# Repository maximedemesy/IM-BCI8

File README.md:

# IM-BCI8

**A low-cost 8-channel wireless EEG / Brain-Computer Interface platform based on the ADS1299 and ESP32-S3.**

> **Project status:** Active development / experimental prototype  
> **Intended use:** Education, research, experimentation and BCI development  
> **Not a medical device**

IM-BCI8 is a personal open-hardware EEG project designed to explore how accessible a complete Brain-Computer Interface platform can be made using readily available components, open-source hardware, 3D printing and modern development tools.

The system combines an **8-channel ADS1299 analog front-end**, an **ESP32-S3**, battery operation, Wi-Fi connectivity, a browser-based acquisition interface and a dry-electrode headset based on the **OpenBCI Ultracortex Mark IV**.

The goal of this repository is to make the complete prototype reproducible and understandable: electronics, firmware, assembly information, mechanical files, characterization data and troubleshooting procedures are progressively being documented here.

---

## Why this project?

IM-BCI8 originally started as a personal side project and as a gift, but quickly evolved into a broader engineering experiment.

Commercial EEG platforms can make experimenting with Brain-Computer Interfaces expensive, particularly for students, makers and independent developers.

The **OpenBCI ecosystem and Cyton board were major inspirations for this project**. Their work demonstrated how open hardware can make biosignal acquisition considerably more accessible.

IM-BCI8 does not aim to replace OpenBCI.

Instead, it explores a more integrated and low-cost architecture focused on:

- low prototype cost;
- simple wireless operation;
- no external acquisition dongle;
- a browser-based user interface hosted directly by the device;
- compatibility with an existing open-source 3D-printable headset;
- dry-electrode experimentation;
- easy modification of both hardware and firmware.

The current prototype costs approximately **$150 USD for the PCB and electronic components** in one-off quantities.

The complete headset adds approximately **$70 USD**, including dry electrodes, wiring, springs, mechanical hardware and 3D-printing material.

This puts the current complete experimental setup at roughly **$220 USD in material cost**.

These figures are approximate prototype costs and exclude assembly labor, tools, shipping, import duties and development time.

---

## System architecture

The current platform is built around a relatively simple architecture:

```text
Dry EEG electrodes
        │
        ▼
   Input filtering
        │
        ▼
     ADS1299
  8-channel AFE
        │
       SPI
        │
        ▼
    ESP32-S3
        │
        ├── Wi-Fi
        ├── Web interface
        ├── Recording
        └── OTA updates

LiPo battery
    │
    ├── 3.3 V digital rail
    ├── 3.3 V analog rail
    └── ~5 V analog rail

USB-C
    │
    ├── Firmware / development
    └── LiPo charging
```

---

## Current hardware

The current IM-BCI8 prototype includes:

- 8 EEG acquisition channels
- Texas Instruments ADS1299 24-bit biopotential analog front-end
- ESP32-S3 microcontroller
- 250 samples per second acquisition
- Wi-Fi communication
- Integrated web interface hosted directly by the ESP32
- Wireless firmware updates
- Single-cell LiPo battery operation
- Integrated battery charger
- Common reference electrode
- BIAS electrode
- Dry EEG electrodes
- Compatibility with a 3D-printable Ultracortex-based headset

The current electrode layout used during development is:

`Fp1 — Fp2 — C3 — C4 — P7 — P8 — O1 — O2`

with separate reference and BIAS electrodes.

---

## Browser-based interface

One of the main design goals of IM-BCI8 is reducing the amount of software required to start experimenting.

The ESP32-S3 hosts its own Wi-Fi network and web interface.

A computer or smartphone can therefore connect directly to the board and access the acquisition interface from a standard web browser.

The current interface provides:

- eight-channel live EEG visualization;
- separated channel plots and individual channel identification;
- configurable signal scaling;
- FFT / frequency-spectrum visualization;
- Delta, Theta, Alpha and Beta band visualization;
- electrode mapping;
- internal ADS1299 test modes;
- experimental event markers;
- CSV recording;
- firmware configuration;
- OTA firmware updates.

No dedicated acquisition dongle is required.

---

## Headset and mechanical design

The headset itself was **not designed as part of IM-BCI8**.

The current prototype uses the official 3D-printable files from the **OpenBCI Ultracortex Mark IV**, together with community-developed electrode-holder designs.

These existing open-source mechanical designs made it possible to focus the project primarily on the electronics, firmware, integration and experimentation rather than redesigning an EEG headset from scratch.

Most of the mechanical components used in the current build therefore originate from the OpenBCI ecosystem or community contributions.

One part had to be recreated specifically for this prototype: a **comfort electrode-holder tip / insert**, because the exact part required for the selected electrode mount could not be found as an available printable file.

The IM-BCI8 electronics enclosure and its integration with the headset are also documented separately where applicable.

All third-party mechanical files included or referenced by this repository will retain appropriate attribution and licensing information.

The current headset uses approximately **$70 USD of material and components**, including:

- dry electrodes;
- wiring;
- springs;
- screws and mechanical hardware;
- reference / BIAS contacts;
- 3D-printing material.

Detailed sourcing and assembly information will be provided in the `mechanical/` and `docs/` directories.

---

## AI-assisted development

Artificial intelligence played a significant role in the development of this project.

This is a personal side project, and one of my priorities was to iterate quickly and explore ideas without spending unnecessary time on repetitive development tasks.

Tools including **OpenAI GPT-5.6** and **Google Gemini** were used throughout different stages of the project, including:

- brainstorming and architecture discussions;
- hardware-design review;
- datasheet interpretation and design checks;
- firmware development;
- web-interface development;
- debugging;
- documentation;
- repository organization;
- test-procedure development.

A significant portion of the ESP32 firmware and browser interface was developed using an AI-assisted, or effectively **“vibe-coded,”** workflow.

AI assistance was also used when discussing and refining parts of the electronic architecture and when preparing documentation for this repository.

This does **not** mean that generated output was assumed to be correct.

Hardware decisions were checked against datasheets and measurements, firmware was tested on the actual device, and the behavior of the complete system was progressively validated experimentally.

AI is treated here as a development and prototyping tool rather than as a substitute for engineering verification.

I am documenting this explicitly because transparency about how the project was created is part of the open-source philosophy of IM-BCI8.

---

## Current development status

IM-BCI8 is **not a finished commercial product**.

The first hardware prototype is operational and the complete acquisition chain has been successfully tested, but characterization is still ongoing.

Current and planned validation work includes:

- electrical characterization;
- input-referred noise measurements;
- frequency-response measurements;
- channel-to-channel crosstalk;
- long-term stability;
- dry-electrode performance;
- BIAS performance;
- real EEG acquisition;
- repeatability across additional boards;
- firmware and web-interface improvements.

Raw characterization data and test procedures will progressively be added to this repository.

---

## Known design limitations

This first hardware revision was deliberately designed around simplicity, compactness and low cost.

It therefore has several known limitations that are important to understand before reproducing it.

### Battery polarity

The current revision does **not** include reverse-polarity protection on the battery input.

Connecting the battery with reversed polarity may permanently damage components.

Battery connector polarity must therefore be verified before power is applied.

### Input and component protection

The design intentionally keeps the analog front-end relatively minimal.

The EEG inputs and several sensitive components are not protected to the level expected from commercial or certified biomedical instrumentation.

Incorrect wiring, electrostatic discharge, inappropriate external equipment or accidental overvoltage may damage the board.

### Galvanic isolation

The current design does **not** provide medical-grade galvanic isolation between the USB interface and the EEG electronics.

For this reason, USB must not be connected while the system is attached to a person.

### Battery monitoring

Battery voltage is not currently measured by the ESP32.

A future revision may include a dedicated battery-voltage sensing circuit.

### Prototype robustness

This board was designed as an experimental prototype rather than as a consumer product.

Some design choices prioritize:

- minimal component count;
- compactness;
- cost;
- ease of fabrication;
- rapid iteration;

over protection against every possible misuse.

These limitations are not hidden issues: they are documented here both for safety and as potential improvement targets for future hardware revisions.

---

## ⚠️ Safety

**IM-BCI8 is experimental hardware and is not a medical device.**

When electrodes are connected to a person, the system must operate from its internal battery only.

Do not connect the board simultaneously to:

- USB;
- a charger;
- a laboratory power supply;
- a grounded oscilloscope;
- a function generator;
- other grounded laboratory equipment.

Human EEG acquisition should use:

**battery power + wireless communication only.**

Anyone reproducing or modifying this project is responsible for understanding the electrical and biological safety implications of their modifications.

A more complete safety document is available in [`SAFETY.md`](SAFETY.md).

---

## Repository structure

```text
IM-BCI8/
├── README.md
├── SAFETY.md
├── .gitignore
│
├── hardware/
│   ├── README.md
│   ├── kicad/
│   │   ├── IM-BCI8_RevA.kicad_pro
│   │   ├── IM-BCI8_RevA.kicad_sch
│   │   └── IM-BCI8_RevA.kicad_pcb
│   │
│   └── manufacturing/
│       ├── README.md
│       ├── BOM/
│       │   └── IM-BCI8_RevA_BOM.csv
│       └── gerbers/
│           └── IM-BCI8_RevA_Gerbers.zip
│
├── firmware/
│   ├── README.md
│   └── IM_BCI8_V1_3_1/
│       ├── IM_BCI8_V1_3_1.ino
│       └── secrets.example.h
│
├── mechanical/
│   ├── README.md
│   │
│   ├── derived/
│   │   └── IM-BCI8_Comfort_Tip.STL
│   │
│   ├── enclosure/
│   │   ├── IM-BCI8_Enclosure_Body.STL
│   │   └── IM-BCI8_Enclosure_Cover.STL
│   │
│   ├── earclip/
│   │   └── IM-BCI8_Compliant_Earclip.STL
│   │
│   └── upstream/
│       └── openbci-ultracortex-mark-iv/
│           ├── LICENSE.md
│           ├── UPSTREAM.md
│           │
│           ├── frame/
│           │   ├── M4_Medium_Front.stl
│           │   └── M4_Medium_Back.stl
│           │
│           ├── inserts/
│           │   └── M4_Hardware_insert_105dot5_percent.STL
│           │
│           ├── clips/
│           │   └── M4_Wire_Clip.stl
│           │
│           └── electrode-holders/
│               ├── M4_Hardware_09_Eholder.STL
│               └── M4_Hardware_09_Octabolt.STL
│
└── docs/
    └── images/
        ├── architecture.png
        ├── characterization-noise.png
        ├── headset-overview.jpg
        ├── im-bci8-hero.jpg
        └── web-interface.png
```

### `hardware/`

KiCad source files, schematics, PCB layout, BOM and manufacturing files.

### `firmware/`

ESP32-S3 firmware and the embedded browser interface.

### `mechanical/`

Mechanical files required to reproduce the current headset configuration, together with attribution to the original OpenBCI and community designs.

### `docs/`

Assembly instructions, flashing procedures, electrode wiring, first-start procedures and troubleshooting.

### `characterization/`

Measurement procedures, raw data and results used to characterize the electronics and complete system.

### `examples/`

Example EEG recordings and simple experiments performed using the platform.

---

## Open development

IM-BCI8 is intended to remain an open project.

Hardware improvements, firmware features, mechanical improvements, analysis tools, experiments and characterization data are welcome.

If you reproduce the board, test a modification, identify a design problem or develop an improvement, please consider opening an Issue or submitting a Pull Request.

Examples of useful contributions include:

- hardware protection improvements;
- analog front-end improvements;
- firmware optimization;
- additional signal-processing tools;
- BrainFlow / LSL / MNE integration;
- improved browser visualization;
- alternative electrode systems;
- additional characterization;
- replicated measurements on independently built boards;
- documentation improvements.

The project is still evolving, and community feedback is part of the development process.

---

## Roadmap

Potential future developments include:

- additional electrical characterization;
- validation on multiple independently assembled boards;
- improved battery monitoring;
- improved input and power protection;
- external BCI software integration;
- improved signal-processing tools;
- additional EEG experiments;
- SSVEP and other BCI demonstrations;
- improved mechanical integration;
- preparation of a second hardware revision based on testing and community feedback.

---

## Reproducing the project

The long-term goal of this repository is to make the complete setup reproducible from publicly available files.

The documentation will progressively include:

1. PCB ordering and component sourcing
2. PCB assembly
3. Visual inspection
4. Power-rail validation
5. ESP32 flashing
6. ADS1299 internal self-tests
7. Channel-by-channel electrical validation
8. Headset printing and assembly
9. Electrode installation and wiring
10. REF and BIAS installation
11. First battery-powered acquisition
12. Troubleshooting
13. Basic EEG validation experiments

The same procedures used during development of the original prototype will be documented whenever possible.

---

## License and attribution

Licensing information for the original IM-BCI8 hardware, firmware and documentation will be finalized before the first official release.

Third-party files and derivative works will retain the attribution and licensing requirements of their respective upstream projects.

The mechanical headset used for the current prototype is based on the **OpenBCI Ultracortex Mark IV** and associated community designs.

The IM-BCI8 electronics are heavily inspired by the OpenBCI Cyton architecture and the wider OpenBCI ecosystem.

IM-BCI8 is an independent personal project and is not affiliated with or endorsed by OpenBCI.

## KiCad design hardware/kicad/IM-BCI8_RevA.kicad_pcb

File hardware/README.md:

# IM-BCI8 Hardware

This document describes the electronic architecture of the first IM-BCI8 hardware revision (**Rev.A**).

The goal of Rev.A was not to design a certified biomedical instrument. It was to build a compact, low-cost and reproducible 8-channel EEG acquisition board around the ADS1299, integrate wireless communication and battery operation, and leave enough flexibility for continued firmware and hardware experimentation.

> **Status:** Rev.A prototype assembled and operational  
> **Use case:** Experimental EEG / BCI development  
> **Not a medical device**

For safety requirements, limitations and human-use rules, see [`../SAFETY.md`](../SAFETY.md).

---

## 1. Design goals

The main design targets for Rev.A were:

- 8 simultaneous EEG channels;
- ADS1299-based biopotential acquisition;
- wireless operation without an external acquisition dongle;
- direct browser access through an ESP32-S3;
- single-cell LiPo operation;
- integrated battery charging;
- compact PCB size;
- low component count and low one-off prototype cost;
- fully editable KiCad sources;
- simple reproduction with commonly available PCB manufacturing services.

The design intentionally prioritizes **cost, integration and simplicity** over protection against every possible misuse.

That trade-off is documented throughout this repository rather than hidden.

---

## 2. High-level architecture

```text
             CH1 ... CH8
                  │
            4.7 kΩ / 4.7 nF
                  │
                  ▼
             ┌─────────┐
REF / SRB1 ─►│         │
BIAS ◄───────│ ADS1299 │
             │         │
             └────┬────┘
                  │ SPI
                  ▼
             ┌───────────┐
             │ ESP32-S3  │
             │  N8R8     │
             └─────┬─────┘
                   │
        ┌──────────┼──────────┐
        │          │          │
      Wi-Fi      Web UI      OTA
```

Power is generated from a single-cell LiPo battery using three separate rails:

```text
LiPo / VBAT
   │
   ├── AP2112K-3.3 ─────────────► +3V3_DIG ─► ESP32-S3
   │
   ├── LP5907MFX-3.3 ───────────► +3V3_AFE ─► ADS1299 DVDD
   │
   └── TPS61099 adjustable
          │
          ▼
       +5V_BOOST
          │
       ferrite
          │
          ▼
       +5V_AFE ─────────────────► ADS1299 AVDD / AVDD1
```

The analog and digital 3.3 V rails are therefore generated by separate regulators.

---

## 3. Main components

| Function | Component | Notes |
| --- | --- | --- |
| EEG analog front-end | **Texas Instruments ADS1299** | 8-channel, 24-bit biopotential AFE |
| Main MCU / radio | **ESP32-S3-WROOM-1-N8R8** | Wi-Fi, web server, acquisition control and OTA |
| Digital 3.3 V regulator | **AP2112K-3.3** | Supplies the ESP32-S3 domain |
| AFE 3.3 V regulator | **LP5907MFX-3.3** | Low-noise rail for ADS1299 DVDD |
| Analog boost | **TPS61099DRV** | Adjustable boost used to generate the analog supply |
| Analog rail filtering | **BLM18KG601BH1D** | Ferrite between `+5V_BOOST` and `+5V_AFE` |
| LiPo charger | **MCP73831-2-OT** | Single-cell linear LiPo charger |
| USB ESD protection | **USBLC6-2SC6** | Protects USB D+ / D- |
| Battery connector | 2-pin connector | `VBAT` + GND |
| EEG connector | 10-pin connector | BIAS, REF and eight channels |

The selected ESP32 module is the **N8R8** variant used on the current PCB.

---

## 4. ADS1299 analog front-end

The ADS1299 is the core of the acquisition board.

Rev.A uses:

- all 8 positive channel inputs;
- the internal SRB1 switching architecture for a common reference;
- the ADS1299 BIAS amplifier;
- internal reference operation;
- external analog and digital supply rails;
- SPI communication with the ESP32-S3.

The current firmware operates the board at **250 samples per second** during normal EEG acquisition.

The hardware itself is not conceptually limited to 250 SPS; this is the current firmware operating point and was selected as a practical EEG default.

### ADS1299 supply configuration

The final Rev.A schematic uses:

```text
AVDD / AVDD1  → +5V_AFE
DVDD           → +3V3_AFE
AVSS / DGND    → GND
CLKSEL         → +3V3_AFE
PWDN           → +3V3_AFE
CLK            → GND
DAISY_IN       → GND
RESV1          → GND
```

`PWDN` is therefore held high in Rev.A and is **not controlled by the ESP32**.

`RESET`, `START` and `CS` are externally controlled, with passive default-state resistors on the ADS1299 control lines.

### Internal support capacitors

The ADS1299 internal reference and charge-pump nodes use the following values in Rev.A:

| Node | Rev.A value |
| --- | ---: |
| VCAP1 | 100 µF polymer |
| VCAP2 | 1 µF |
| VCAP3 | 1 µF + 100 nF |
| VCAP4 | 1 µF |
| VREFP–VREFN | 10 µF + 100 nF |

These capacitors were placed close to the corresponding ADS1299 pins because these nodes are particularly sensitive to layout and supply noise.

---

## 5. EEG inputs

Each of the eight external signal channels follows the same basic topology:

```text
Electrode
   │
 4.7 kΩ
   │
   ├────────► ADS1299 INxP
   │
 4.7 nF
   │
  GND
```

The 4.7 kΩ / 4.7 nF network is mainly used for input current limiting and high-frequency filtering.

It should **not** be interpreted as complete medical-grade input protection.

The negative channel inputs are not routed to individual external electrodes. During normal referential acquisition, the firmware uses the ADS1299 internal SRB1 switching to connect the channel negative inputs to the common reference.

### External connector J2

| J2 pin | Function |
| ---: | --- |
| 1 | BIAS |
| 2 | REF / SRB1 |
| 3 | CH1 |
| 4 | CH2 |
| 5 | CH3 |
| 6 | CH4 |
| 7 | CH5 |
| 8 | CH6 |
| 9 | CH7 |
| 10 | CH8 |

The current development headset maps the eight signal channels to:

```text
CH1 → Fp1
CH2 → Fp2
CH3 → C3
CH4 → C4
CH5 → P7
CH6 → P8
CH7 → O1
CH8 → O2
```

This mapping is a current experimental configuration, not a hardware restriction.

---

## 6. Reference / SRB1 path

The common reference electrode enters through J2 pin 2.

Rev.A uses:

```text
REF electrode
     │
   4.7 kΩ
     │
     ├────────► SRB1
     │
   4.7 nF
     │
    GND
```

This gives the reference path a filtering topology similar to the eight signal inputs.

The SRB1 connection is then enabled or disabled by firmware depending on the selected ADS1299 acquisition mode.

---

## 7. BIAS circuit

The ADS1299 BIAS output is exposed on J2 pin 1 through a 4.7 kΩ series resistor.

The Rev.A BIAS compensation network is:

```text
BIASOUT ──┬── 1 MΩ ──┐
          │           │
          └── 1.5 nF ─┤
                      │
                   BIASINV
```

and:

```text
BIASOUT ── 4.7 kΩ ──► J2 pin 1 / BIAS electrode
```

BIAS can be enabled or disabled by firmware.

The current firmware intentionally allows the board to be tested first with BIAS disabled, then compared with BIAS enabled once the basic electrode/reference path is confirmed.

---

## 8. ESP32-S3 and digital interface

Rev.A uses an **ESP32-S3-WROOM-1-N8R8** module.

The ESP32 handles:

- ADS1299 configuration;
- SPI acquisition;
- DRDY synchronization;
- buffering;
- Wi-Fi access point operation;
- browser interface hosting;
- CSV acquisition support;
- OTA firmware updates;
- status LED control.

### ADS1299 ↔ ESP32-S3 mapping

| ADS1299 signal | ESP32-S3 GPIO |
| --- | ---: |
| START | GPIO8 |
| RESET | GPIO9 |
| CS | GPIO10 |
| MOSI / DIN | GPIO11 |
| SCLK | GPIO12 |
| MISO / DOUT | GPIO13 |
| DRDY | GPIO14 |

The current firmware uses a deliberately modest SPI clock for robust bring-up and acquisition.

### Status LED

D1 is connected to **GPIO4** through a 1 kΩ resistor.

It is available as a firmware-controlled status indicator.

### Boot control

GPIO0 includes a 10 kΩ pull-up and a physical push button for manual boot/programming support.

---

## 9. Power architecture

Power integrity was one of the main design concerns because the board combines a Wi-Fi MCU, a switching converter and a low-noise biopotential AFE.

### `+3V3_DIG`

```text
VBAT
  │
AP2112K-3.3
  │
+3V3_DIG
  │
ESP32-S3
```

This rail supplies the digital / wireless domain.

### `+3V3_AFE`

```text
VBAT
  │
LP5907MFX-3.3
  │
+3V3_AFE
  │
ADS1299 DVDD
```

A separate low-noise regulator is used for the ADS1299 digital supply rather than sharing the ESP32 rail.

### `+5V_AFE`

The ADS1299 analog supply is generated by an adjustable TPS61099 boost converter.

The feedback divider is:

```text
390 kΩ / 100 kΩ
```

which targets approximately **4.9 V** before analog filtering.

The raw boost rail is named:

```text
+5V_BOOST
```

and then passes through a **BLM18KG601BH1D ferrite bead** to create:

```text
+5V_AFE
```

used by the ADS1299 analog supply pins.

The first assembled prototype measured the analog rail close to the intended value during bring-up.

---

## 10. Power switch strategy

Rev.A does not route the entire board current through the mechanical switch.

Instead, SW2 is used as a logic-level enable selector:

```text
SW2 ON
PWR_EN = VBAT
→ regulators enabled
→ board ON

SW2 OFF
PWR_EN = GND
→ regulators disabled
→ board OFF
```

`PWR_EN` also has a 100 kΩ pull-down.

This architecture allows the battery charger to remain connected to the cell while the rest of the system is switched off.

As a result:

```text
USB connected
+
SW2 OFF
=
battery can charge while the EEG electronics remain off
```

This was a deliberate design choice.

---

## 11. USB-C and battery charging

USB-C serves two development functions:

- ESP32-S3 USB programming / communication;
- LiPo charging.

### Native ESP32-S3 USB

The native ESP32-S3 USB signals use:

```text
USB D- → USBLC6 → 22 Ω → GPIO19
USB D+ → USBLC6 → 22 Ω → GPIO20
```

The USB-C CC pins use 5.1 kΩ pull-down resistors.

### LiPo charging

VBUS feeds an **MCP73831-2-OT** charger.

Rev.A uses:

```text
RPROG = 2 kΩ
```

corresponding to a nominal charge-current configuration of approximately 500 mA for the selected charger configuration.

The battery used with the system must therefore be suitable for the configured charging current.

The charger uses 4.7 µF local capacitors on its VDD and VBAT sides.

### Charge indicator

D2 is connected to the MCP73831 `STAT` output through a 1 kΩ resistor from `VBUS_USB`.

Expected behavior:

```text
USB absent                  → D2 OFF
USB present, charging       → D2 ON
charge terminated / full    → D2 OFF
```

The MCP73831 is a charger, not a complete power-path controller.

For normal use, charging the battery with the main electronics switched off is preferred.

---

## 12. Important safety architecture

There is **no galvanic isolation between USB ground and the EEG electronics** in Rev.A.

This means that the USB port must be treated as a development / charging interface, not as a simultaneously connected interface during human EEG acquisition.

When electrodes are connected to a person:

```text
USB disconnected
charger disconnected
laboratory PSU disconnected
grounded oscilloscope disconnected
function generator disconnected
battery power only
wireless communication only
```

This limitation is fundamental to Rev.A and is not solved by firmware.

See [`../SAFETY.md`](../SAFETY.md) before reproducing or using the hardware.

---

## 13. Rev.A design trade-offs and known limitations

Rev.A was intentionally kept compact and relatively minimal.

### What Rev.A prioritizes

- low one-off cost;
- small component count;
- compact integration;
- integrated Wi-Fi;
- integrated charging;
- easy firmware iteration;
- straightforward PCB reproduction;
- accessibility for experimental BCI work.

### What Rev.A does not provide

- reverse-polarity protection on the battery connector;
- medical-grade galvanic isolation;
- medical-grade input protection;
- dedicated battery-voltage measurement;
- a true charger / system power-path controller;
- protection against every possible wiring or handling error;
- certification as biomedical or consumer equipment.

The absence of reverse-polarity protection is particularly important: **battery polarity must be checked before connection**.

The 4.7 kΩ input resistors and RC networks must not be interpreted as sufficient patient-protection circuitry for a certified medical device.

The current board should be treated as **experimental laboratory / maker hardware**.

---

## 14. Rev.A bring-up status

The first assembled Rev.A board has successfully passed the main bring-up stages:

- digital 3.3 V rail operation;
- AFE 3.3 V rail operation;
- boosted analog rail operation;
- ESP32-S3 boot and Wi-Fi operation;
- ADS1299 SPI identification;
- ADS1299 internal test signal;
- ADS1299 internal short/noise testing;
- all eight physical signal paths;
- external signal acquisition across all eight channels;
- battery operation;
- USB charging;
- browser-based acquisition;
- OTA firmware update.

Detailed measurement protocols and raw characterization data are kept separate from this hardware document and belong in [`../characterization/`](../characterization/).

This separation is intentional: the hardware documentation describes **what the board is**, while the characterization section describes **how well it performs**.

---

## 15. Manufacturing cost

The Rev.A PCB and electronic components cost approximately:

**~$150 USD in one-off prototype quantities**

This number is intended as an order-of-magnitude reproducibility figure rather than a guaranteed BOM price.

It excludes:

- soldering / assembly labor;
- tools;
- shipping;
- import duties and taxes;
- failed parts or spare components;
- development time.

A structured Rev.A BOM is available in
[`manufacturing/BOM/IM-BCI8_RevA_BOM.csv`](manufacturing/BOM/IM-BCI8_RevA_BOM.csv).

---

## 16. Hardware files

The intended structure of this directory is:

```text
hardware/
├── README.md
├── kicad/
│   ├── IM-BCI8_RevA.kicad_pro
│   ├── IM-BCI8_RevA.kicad_sch
│   └── IM-BCI8_RevA.kicad_pcb
│
├── manufacturing/
│   ├── gerbers/
│   ├── BOM/
│   └── README.md
│
└── images/
```

### `kicad/`

Editable design sources.

These are the files to use when studying or modifying the board.

### `manufacturing/`

Production-oriented files intended for reproducing a known hardware revision without editing the design.

Manufacturing packages should always be associated with a clear hardware revision or GitHub release.

---

## 17. Rev.B candidates

Rev.A is intentionally being characterized before a second board revision is frozen.

Potential Rev.B improvements currently include:

- battery reverse-polarity protection;
- battery-voltage sensing by the ESP32;
- improved input protection;
- additional ESD protection where appropriate;
- review of charger / system power-path behavior;
- additional hardware test points;
- improvements suggested by Rev.A characterization and community feedback.

These are candidates, not promises: changes should be driven by measured limitations rather than added only for feature count.

---

## 18. Reproduction philosophy

The goal of publishing the hardware is not only to provide Gerbers.

A reproducible open-hardware project should make it possible to understand:

1. what each circuit block does;
2. which compromises were made;
3. how the board should be assembled;
4. how the first power-up should be performed;
5. which measurements indicate correct operation;
6. which known failure modes exist;
7. how a modified design differs from the tested reference.

For that reason, assembly, bring-up and troubleshooting are documented separately instead of being compressed into this file.

---

## Attribution

The IM-BCI8 electronics are heavily inspired by the OpenBCI Cyton architecture and the wider OpenBCI ecosystem.

Rev.A is an independent implementation built around the ADS1299 and ESP32-S3, with a different power, communication and user-interface architecture.

IM-BCI8 is not affiliated with or endorsed by OpenBCI.

Licensing and detailed third-party attribution will be finalized before the first official hardware release.

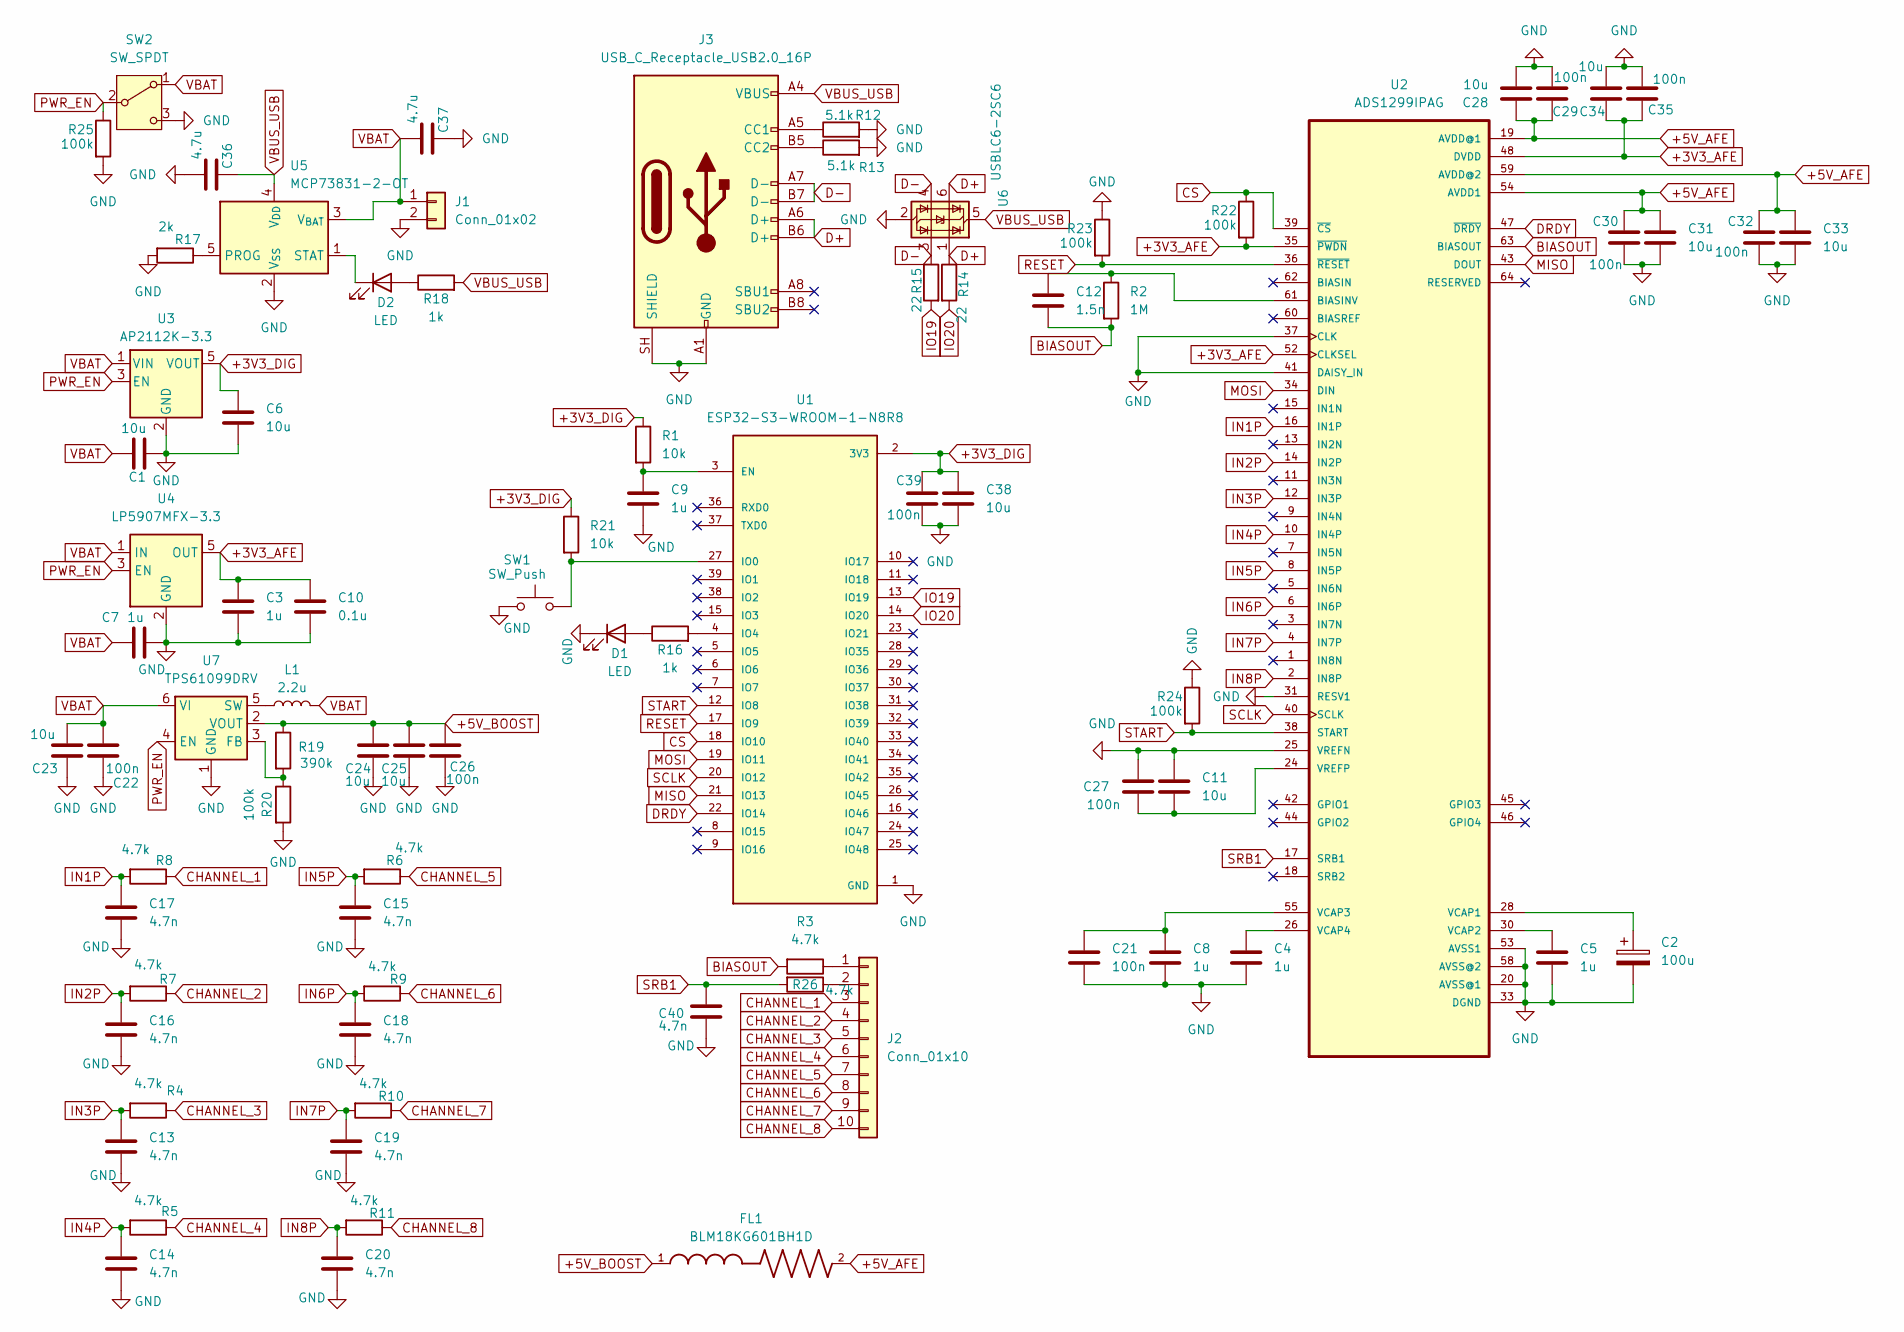
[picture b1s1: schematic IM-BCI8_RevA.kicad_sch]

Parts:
C1, C6: 10u; C_0603_1608Metric
C2: 100u; CP_EIA-3528-21_Kemet-B
C3, C4, C5, C7, C8, C9: 1u; C_0603_1608Metric
C10: 0.1u; C_0603_1608Metric
C11, C23, C24, C25, C28, C31, C33, C34, C38: 10u; C_1206_3216Metric
C12: 1.5n; C_0603_1608Metric
C13, C14, C15, C16, C17, C18, C19, C20, C40: 4.7n; C_0805_2012Metric
C21, C22, C26, C27, C29, C30, C32, C35, C39: 100n; C_0603_1608Metric
C36, C37: 4.7u; C_0603_1608Metric
D1, D2: LED; LED_0603_1608Metric
FL1: BLM18KG601BH1D; R_0603_1608Metric
J1: Conn_01x02; JST_PH_S2B-PH-K_1x02_P2.00mm_Horizontal
J2: Conn_01x10; PinSocket_1x10_P2.54mm_Horizontal
J3: USB_C_Receptacle_USB2.0_16P; USB_C_Receptacle_HRO_TYPE-C-31-M-12
L1: 2.2u; L_1008_2520Metric
R1, R21: 10k; R_0603_1608Metric
R2: 1M; R_0603_1608Metric
R3, R4, R5, R6, R7, R8, R9, R10, R11, R26: 4.7k; R_0603_1608Metric
R12, R13: 5.1k; R_0603_1608Metric
R14, R15: 22; R_0603_1608Metric
R16, R18: 1k; R_0603_1608Metric
R17: 2k; R_0603_1608Metric
R19: 390k; R_0603_1608Metric
R20, R22, R23, R24, R25: 100k; R_0603_1608Metric
SW1: SW_Push; SW_SPST_Omron_B3FS-100xP
SW2: SW_SPDT; SW_SPDT_PCM12
U1: ESP32-S3-WROOM-1-N8R8; XCVR_ESP32S3WROOM1N8R8
U2: ADS1299IPAG; QFP50P1200X1200X120-64N
U3: AP2112K-3.3; SOT-23-5
U4: LP5907MFX-3.3; SOT-23-5
U5: MCP73831-2-OT; SOT-23-5
U6: USBLC6-2SC6; SOT-23-6
U7: TPS61099DRV; WSON-6-1EP_2x2mm_P0.65mm_EP1x1.6mm

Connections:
+3V3_AFE: C3.1, C10.1, C34.1, C35.1, R22.2, U2.35 (~PWDN), U2.48 (DVDD), U2.50 (DVDD), U2.52 (CLKSEL), U4.5 (OUT)
+3V3_DIG: C6.1, C38.1, C39.1, R1.1, R21.1, U1.2 (3V3), U3.5 (VOUT)
+5V_AFE: C28.1, C29.1, C30.1, C31.1, C32.1, C33.1, FL1.2, U2.19 (AVDD@1), U2.21 (AVDD@1), U2.22 (AVDD@1), U2.54 (AVDD1), U2.56 (AVDD@1), U2.59 (AVDD@2)
+5V_BOOST: C24.1, C25.1, C26.1, FL1.1, R19.1, U7.2 (VOUT)
BIASOUT: C12.2, R2.2, R3.2, U2.63 (BIASOUT)
CHANNEL_1: J2.3, R8.1
CHANNEL_2: J2.4, R7.1
CHANNEL_3: J2.5, R4.1
CHANNEL_4: J2.6, R5.1
CHANNEL_5: J2.7, R6.1
CHANNEL_6: J2.8, R9.1
CHANNEL_7: J2.9, R10.1
CHANNEL_8: J2.10, R11.1
CS: R22.1, U1.18 (IO10), U2.39 (~CS)
D+: J3.A6 (D+), J3.B6 (D+), R14.1, U6.1 (I/O1), U6.6 (I/O1)
D-: J3.A7 (D-), J3.B7 (D-), R15.1, U6.3 (I/O2), U6.4 (I/O2)
DRDY: U1.22 (IO14), U2.47 (~DRDY)
GND: C1.2, C2.2, C3.2, C4.2, C5.2, C6.2, C7.2, C8.2, C9.2, C10.2, C11.2, C13.2, C14.2, C15.2, C16.2, C17.2, C18.2, C19.2, C20.2, C21.2, C22.2, C23.2, C24.2, C25.2, C26.2, C27.2, C28.2, C29.2, C30.2, C31.2, C32.2, C33.2, C34.2, C35.2, C36.2, C37.1, C38.2, C39.2, C40.1, D1.1 (K), J1.2, J3.A1 (GND), J3.A12 (GND), J3.B1 (GND), J3.B12 (GND), J3.SH (SHIELD), R12.2, R13.2, R17.2, R20.2, R23.1, R24.1, R25.2, SW1.1, SW2.3 (C), U1.1 (GND), U1.40 (GND), U1.41_1 (GND), U1.41_2 (GND), U1.41_3 (GND), U1.41_4 (GND), U1.41_5 (GND), U1.41_6 (GND), U1.41_7 (GND), U1.41_8 (GND), U1.41_9 (GND), U1.41_10, U1.41_11, U1.41_12, U1.41_13, U1.41_14, U1.41_15, U1.41_16, U1.41_17, U1.41_18, U1.41_19, U1.41_20, U1.41_21, U2.20 (AVSS@1), U2.23 (AVSS@1), U2.25 (VREFN), U2.31 (RESV1), U2.32 (AVSS@1), U2.33 (DGND), U2.37 (CLK), U2.41 (DAISY_IN), U2.49 (DGND), U2.51 (DGND), U2.53 (AVSS1), U2.57 (AVSS@1), U2.58 (AVSS@2), U3.2 (GND), U4.2 (GND), U5.2 (V_{SS}), U6.2 (GND), U7.1 (GND), U7.7 (GND)
IN1P: C17.1, R8.2, U2.16 (IN1P)
IN2P: C16.1, R7.2, U2.14 (IN2P)
IN3P: C13.1, R4.2, U2.12 (IN3P)
IN4P: C14.1, R5.2, U2.10 (IN4P)
IN5P: C15.1, R6.2, U2.8 (IN5P)
IN6P: C18.1, R9.2, U2.6 (IN6P)
IN7P: C19.1, R10.2, U2.4 (IN7P)
IN8P: C20.1, R11.2, U2.2 (IN8P)
IO19: R15.2, U1.13 (IO19)
IO20: R14.2, U1.14 (IO20)
MISO: U1.21 (IO13), U2.43 (DOUT)
MOSI: U1.19 (IO11), U2.34 (DIN)
unnamed: D1.2 (A), R16.1
unnamed: D2.2 (A), R18.1
unnamed: D2.1 (K), U5.1 (STAT)
unnamed: J2.1, R3.1
unnamed: J2.2, R26.1
unnamed: J3.A5 (CC1), R12.1
unnamed: J3.B5 (CC2), R13.1
unnamed: C9.1, R1.2, U1.3 (EN)
unnamed: R21.2, SW1.2, U1.27 (IO0)
unnamed: R16.2, U1.4 (IO4)
unnamed: C12.1, R2.1, U2.61 (BIASINV)
unnamed: C2.1, U2.28 (VCAP1)
unnamed: C5.1, U2.30 (VCAP2)
unnamed: C8.1, C21.1, U2.55 (VCAP3)
unnamed: C4.1, U2.26 (VCAP4)
unnamed: C11.1, C27.1, U2.24 (VREFP)
unnamed: R17.1, U5.5 (PROG)
unnamed: R19.2, R20.1, U7.3 (FB)
unnamed: L1.1, U7.5 (SW)
PWR_EN: R25.1, SW2.2 (B), U3.3 (EN), U4.3 (EN), U7.4 (EN)
RESET: R23.2, U1.17 (IO9), U2.36 (~RESET)
SCLK: U1.20 (IO12), U2.40 (SCLK)
SRB1: C40.2, R26.2, U2.17 (SRB1)
START: R24.2, U1.12 (IO8), U2.38 (START)
VBAT: C1.1, C7.1, C22.1, C23.1, C37.2, J1.1, L1.2, SW2.1 (A), U3.1 (VIN), U4.1 (IN), U5.3 (V_{BAT}), U7.6 (VI)
VBUS_USB: C36.1, J3.A4 (VBUS), J3.A9 (VBUS), J3.B4 (VBUS), J3.B9 (VBUS), R18.2, U5.4 (V_{DD}), U6.5 (VBUS)

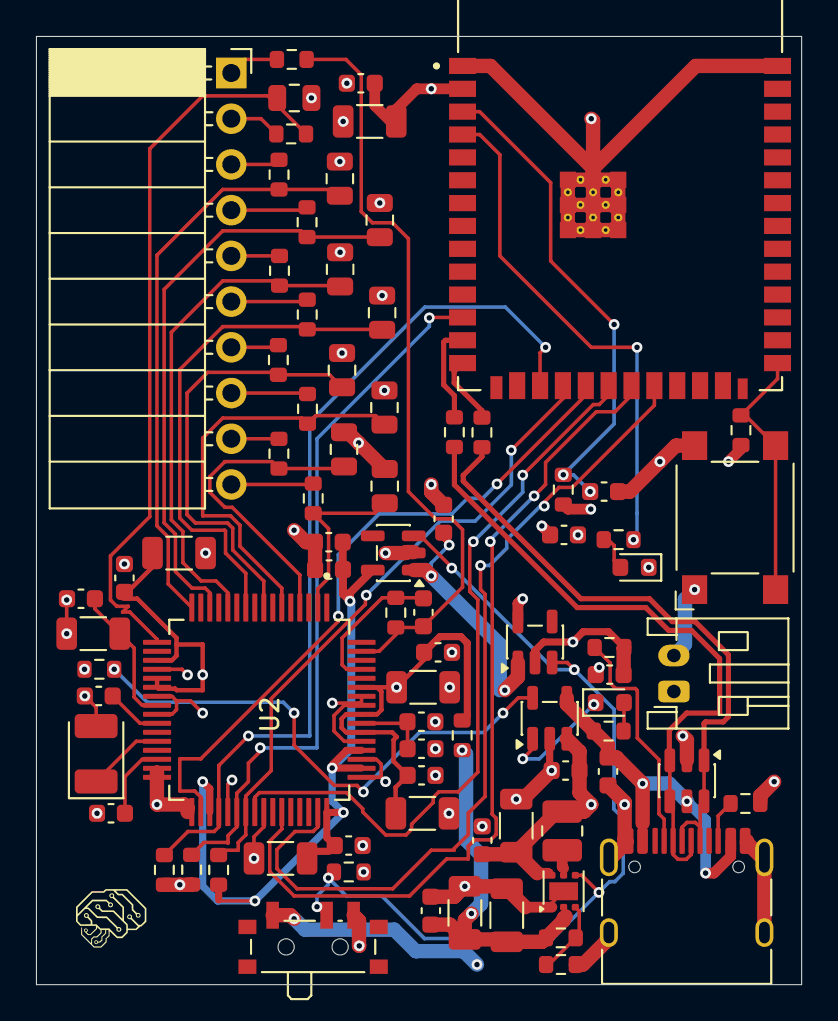
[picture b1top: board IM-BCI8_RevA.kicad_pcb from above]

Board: 4 copper layers, 42.5 x 52.7 mm, 82 parts (0 on the bottom side), 56 nets.

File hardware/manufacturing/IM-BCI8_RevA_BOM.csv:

Reference,Quantity,Value,Manufacturer,Manufacturer Part Number,Supplier,Supplier Part Number,KiCad Footprint,Description,Notes
"C1, C6",2,10 µF,Taiyo Yuden,LMK107BBJ106MALT,DigiKey,587-3258-1-ND,C_0603_1608Metric,10 µF 10 V X5R MLCC,General decoupling / regulator input.
C2,1,100 µF,KEMET,T520B107M006ATE040,DigiKey,399-4008-1-ND,CP_EIA-3528-21_Kemet-B,"100 µF 6.3 V polymer tantalum, low ESR",ADS1299 VCAP1. POLARIZED — observe orientation.
"C3, C4, C5, C7, C8, C9",6,1 µF,KEMET,C0603C105K4RACTU,DigiKey,399-C0603C105K4RACTUCT-ND,C_0603_1608Metric,1 µF 16 V X7R MLCC,
"C10, C21, C22, C26, C27, C29, C30, C32, C35, C39",10,100 nF,TDK,C1608X7R1H104K080AA,DigiKey,445-1314-1-ND,C_0603_1608Metric,100 nF 50 V X7R MLCC,C10 is labelled 0.1 µF in KiCad; same component/value.
"C11, C23, C24, C25, C28, C31, C33, C34, C38",9,10 µF,KEMET,C1206C106K4PACTU,DigiKey,399-C1206C106K4PACTUCT-ND,C_1206_3216Metric,10 µF 16 V X5R MLCC,
C12,1,1.5 nF,YAGEO,CC0603KRX7R9BB152,DigiKey,311-1184-1-ND,C_0603_1608Metric,1.5 nF 50 V X7R MLCC,ADS1299 BIAS compensation network with R2.
"C13, C14, C15, C16, C17, C18, C19, C20, C40",9,4.7 nF,KEMET,C0805C472K5RECAUTO,DigiKey,399-17884-1-ND,C_0805_2012Metric,4.7 nF 50 V X7R MLCC,Input filters; C40 is the SRB1/reference filter.
"C36, C37",2,4.7 µF,KEMET,C0603C475K8PACTU,DigiKey,399-C0603C475K8PACTUCT-ND,C_0603_1608Metric,4.7 µF 10 V X5R MLCC,MCP73831 VDD/VBAT local capacitors.
D1,1,Green LED,ams OSRAM,KT EELP41.12-S2U1-25-2X4Y-5-R18,DigiKey,475-KTEELP41.12-S2U1-25-2X4Y-5-R18CT-ND,LED_0603_1608Metric,Green 0603 LED,Firmware-controlled status LED (GPIO4). POLARIZED.
D2,1,Red LED,Broadcom,ASCKCR00-BU5V5020402,DigiKey,516-ASCKCR00-BU5V5020402CT-ND,LED_0603_1608Metric,Red 0603 LED,MCP73831 charge-status LED. POLARIZED.
FL1,1,600 Ω @ 100 MHz,Murata,BLM18KG601BH1D,DigiKey,490-14032-1-ND,R_0603_1608Metric,"Ferrite bead, 1 A",+5V_BOOST → +5V_AFE filtering.
J1,1,2-pin JST-PH,JST,S2B-PH-K-S,DigiKey,455-1719-ND,JST_PH_S2B-PH-K_1x02_P2.00mm_Horizontal,JST PH 2.0 mm right-angle connector,Battery connector. Rev.A has NO reverse-polarity protection; verify polarity before connection.
J2,1,1×10 socket,Sullins Connector Solutions,PPTC101LGBN-RC,DigiKey,S5446-ND,PinSocket_1x10_P2.54mm_Horizontal,1×10 2.54 mm right-angle female header,"EEG connector: BIAS, REF, CH1…CH8."
J3,1,USB-C USB 2.0,GCT,USB4105-GF-A,DigiKey,2073-USB4105-GF-ACT-ND,USB_C_Receptacle_HRO_TYPE-C-31-M-12,"USB-C receptacle, 16 signal contacts, right-angle",GCT part used for Rev.A; verified compatible with the HRO TYPE-C-31-M-12 footprint.
L1,1,2.2 µH,Würth Elektronik,74404024022,DigiKey,732-5436-1-ND,L_1008_2520Metric,"2.2 µH power inductor, 1.65 A rated",TPS61099 boost inductor.
"R1, R21",2,10 kΩ,Stackpole Electronics,RMCF0603FT10K0,DigiKey,RMCF0603FT10K0CT-ND,R_0603_1608Metric,10 kΩ 1% resistor,
R2,1,1 MΩ,YAGEO,RC0603FR-071ML,DigiKey,311-1.00MHRCT-ND,R_0603_1608Metric,1 MΩ 1% resistor,ADS1299 BIAS compensation network with C12.
"R3, R4, R5, R6, R7, R8, R9, R10, R11, R26",10,4.7 kΩ,YAGEO,RC0603FR-074K7L,DigiKey,311-4.70KHRCT-ND,R_0603_1608Metric,4.7 kΩ 1% resistor,"EEG channel, BIAS and SRB1 series resistors."
"R12, R13",2,5.1 kΩ,Bourns,CR0603-FX-5101ELF,DigiKey,CR0603-FX-5101ELFCT-ND,R_0603_1608Metric,5.1 kΩ 1% resistor,USB-C CC pull-downs.
"R14, R15",2,22 Ω,Stackpole Electronics,RMCF0603FT22R0,DigiKey,RMCF0603FT22R0CT-ND,R_0603_1608Metric,22 Ω 1% resistor,USB D+/D− series resistors near ESP32-S3.
"R16, R18",2,1 kΩ,YAGEO,RC0603FR-071KL,DigiKey,311-1.00KHRCT-ND,R_0603_1608Metric,1 kΩ 1% resistor,LED current limiting.
R17,1,2 kΩ,Panasonic,ERA-3AEB202V,DigiKey,P2.0KDBCT-ND,R_0603_1608Metric,2 kΩ 0.1% resistor,MCP73831 RPROG; configures approximately 500 mA nominal charge current.
R19,1,390 kΩ,YAGEO,RC0603FR-07390KL,DigiKey,311-390KHRCT-ND,R_0603_1608Metric,390 kΩ 1% resistor,TPS61099 feedback divider.
"R20, R22, R23, R24, R25",5,100 kΩ,YAGEO,RC0603FR-07100KL,DigiKey,311-100KHRCT-ND,R_0603_1608Metric,100 kΩ 1% resistor,TPS61099 feedback and logic pull resistors.
SW1,1,Momentary SPST,Omron,B3FS-1000P,DigiKey,SW423CT-ND,SW_SPST_Omron_B3FS-100xP,Tactile push button,ESP32 boot/programming support.
SW2,1,SPDT slide switch,C&K,PCM12SMTR,DigiKey,401-2016-1-ND,SW_SPDT_PCM12,Right-angle SMD SPDT slide switch,"Used as logic-level PWR_EN selector, not as the main current path."
U1,1,ESP32-S3-WROOM-1-N8R8,Espressif Systems,ESP32-S3-WROOM-1-N8R8,DigiKey,5407-ESP32-S3-WROOM-1-N8R8CT-ND,XCVR_ESP32S3WROOM1N8R8,"ESP32-S3 module, 8 MB flash + 8 MB PSRAM",Exact Rev.A module variant.
U2,1,ADS1299,Texas Instruments,ADS1299IPAGR,DigiKey,296-34818-1-ND,QFP50P1200X1200X120-64N,"8-channel, 24-bit biopotential AFE, TQFP-64",Rev.A ordered part. The schematic value may appear as ADS1299IPAG; 'R' denotes tape-and-reel packaging.
U3,1,AP2112K-3.3,Diodes Incorporated,AP2112K-3.3TRG1,DigiKey,AP2112K-3.3TRG1DICT-ND,SOT-23-5,3.3 V 600 mA LDO,+3V3_DIG regulator.
U4,1,LP5907-3.3,Texas Instruments,LP5907MFX-3.3/NOPB,DigiKey,296-38557-1-ND,SOT-23-5,Low-noise 3.3 V 250 mA LDO,+3V3_AFE regulator.
U5,1,MCP73831-2,Microchip Technology,MCP73831T-2ATI/OT,DigiKey,MCP73831T-2ATI/OTCT-ND,SOT-23-5,Single-cell Li-Ion/LiPo linear charger,R17 = 2 kΩ; use a cell compatible with the configured charge current.
U6,1,USBLC6-2SC6,STMicroelectronics,USBLC6-2SC6Y,DigiKey,497-11882-1-ND,SOT-23-6,2-line USB ESD protection,Y suffix is the ordered Rev.A variant.
U7,1,TPS61099,Texas Instruments,TPS61099DRVR,DigiKey,296-TPS61099DRVRCT-ND,WSON-6-1EP_2x2mm_P0.65mm_EP1x1.6mm,Adjustable synchronous boost converter,Generates +5V_BOOST; small exposed-pad package requires careful assembly.
